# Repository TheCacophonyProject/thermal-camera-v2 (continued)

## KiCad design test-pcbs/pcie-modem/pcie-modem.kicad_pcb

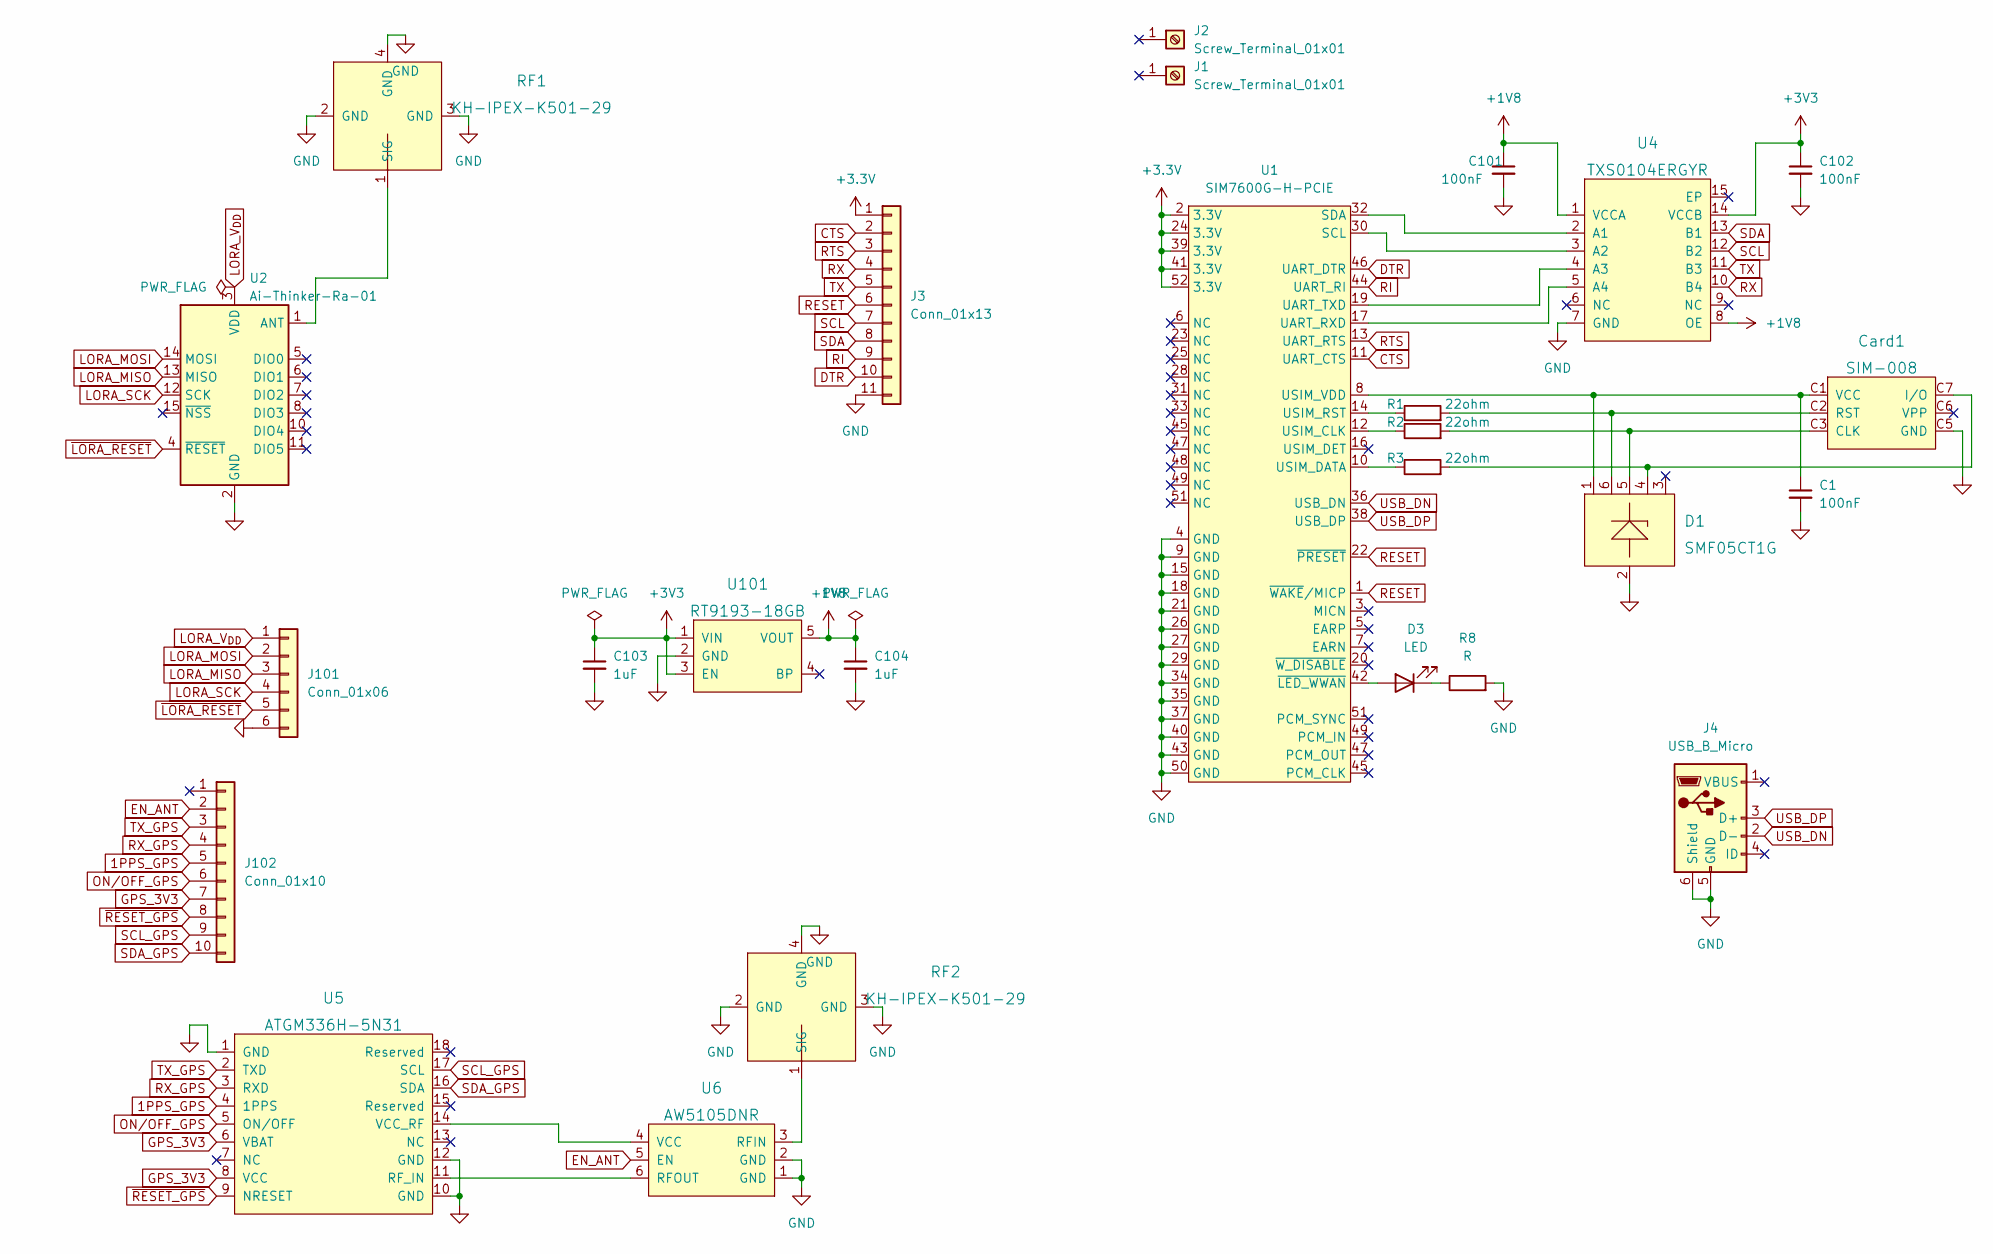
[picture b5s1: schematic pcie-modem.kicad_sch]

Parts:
C1: 100nF; C_0402_1005Metric; LCSC C1525
C101, C102: 100nF; C_0402_1005Metric; LCSC C307331
C103: 1uF; C_0402_1005Metric
C104: 1uF; C_0402_1005Metric; LCSC C52923
Card1: SIM-008; SIM-SMD_SIM-008; LCSC C125618
D1: SMF05CT1G; SOT-363_L2.0-W1.3-P0.65-LS2.1-TL; LCSC C15879
D3: LED; LED_0805_2012Metric; LCSC C84256
J1, J2: Screw_Terminal_01x01; SMD_M2_nut; LCSC C2928176
J3: Conn_01x13; PinHeader_1x11_P2.54mm_Vertical
J4: USB_B_Micro; 920-E52A2021S10100; LCSC C10418
J101: Conn_01x06; PinHeader_1x06_P2.54mm_Vertical
J102: Conn_01x10; PinHeader_1x10_P2.54mm_Vertical
R1, R2, R3: 22ohm; R_0402_1005Metric; LCSC C25092
R8: R; R_0603_1608Metric; LCSC C21190
RF1, RF2: KH-IPEX-K501-29; ANT-SMD_KH-IPEX-K501-29; LCSC C411563
U1: SIM7600G-H-PCIE; BUS_PCI_Express_Mini_Full; LCSC C266898
U2: Ai-Thinker-Ra-01; Ai-Thinker-Ra-01-LoRa; LCSC C90040
U4: TXS0104ERGYR; VQFN-14_L3.5-W3.5-P0.50-BL-EP; JLC Part Extended Part
U5: ATGM336H-5N31; GPSM-SMD_ATGM336H-TR; LCSC C90770
U6: AW5105DNR; DFN-6_L1.5-W1.0-P0.50-BL; LCSC C506193
U101: RT9193-18GB; SOT-23-5; LCSC C27416

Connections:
1PPS_GPS: J102.5, U5.4 (1PPS)
+1V8: C101.1, C104.1, U4.1 (VCCA), U4.8 (OE), U101.5 (VOUT)
CTS: J3.2, U1.11 (UART_CTS)
DTR: J3.10, U1.46 (UART_DTR)
EN_ANT: J102.2, U6.5 (EN)
GND: C1.2, C101.2, C102.2, C103.2, C104.2, Card1.C5 (GND), D1.2, J3.11, J4.5 (GND), J4.6 (Shield), J101.6, R8.2, RF1.2 (GND), RF1.3 (GND), RF1.4 (GND), RF2.2 (GND), RF2.3 (GND), RF2.4 (GND), U1.4 (GND), U1.9 (GND), U1.15 (GND), U1.18 (GND), U1.21 (GND), U1.26 (GND), U1.27 (GND), U1.29 (GND), U1.34 (GND), U1.35 (GND), U1.37 (GND), U1.40 (GND), U1.43 (GND), U1.50 (GND), U2.2 (GND), U2.9 (GND), U2.16 (GND), U4.7 (GND), U5.1 (GND), U5.10 (GND), U5.12 (GND), U6.1 (GND), U6.2 (GND), U101.2 (GND)
GPS_3V3: J102.7, U5.6 (VBAT), U5.8 (VCC)
LORA_MISO: J101.3, U2.13 (MISO)
LORA_MOSI: J101.2, U2.14 (MOSI)
LORA_SCK: J101.4, U2.12 (SCK)
LORA_V_{DD}: J101.1, U2.3 (VDD)
unnamed: C1.1, Card1.C1 (VCC), D1.1, U1.8 (USIM_VDD)
unnamed: Card1.C2 (RST), D1.6, R1.2
unnamed: Card1.C3 (CLK), D1.5, R2.2
unnamed: Card1.C7 (I/O), D1.4, R3.2
unnamed: D3.1 (K), R8.1
unnamed: D3.2 (A), U1.42 (~LED_WWAN)
unnamed: R1.1, U1.14 (USIM_RST)
unnamed: R2.1, U1.12 (USIM_CLK)
unnamed: R3.1, U1.10 (USIM_DATA)
unnamed: RF1.1 (SIG), U2.1 (ANT)
unnamed: RF2.1 (SIG), U6.3 (RFIN)
unnamed: U1.17 (UART_RXD), U4.5 (A4)
unnamed: U1.19 (UART_TXD), U4.4 (A3)
unnamed: U1.30 (SCL), U4.3 (A2)
unnamed: U1.32 (SDA), U4.2 (A1)
unnamed: U5.11 (RF_IN), U6.6 (RFOUT)
unnamed: U5.14 (VCC_RF), U6.4 (VCC)
ON/OFF_GPS: J102.6, U5.5 (ON/OFF)
RESET: J3.6, U1.1 (~WAKE/MICP), U1.22 (~PRESET)
RI: J3.9, U1.44 (UART_RI)
RTS: J3.3, U1.13 (UART_RTS)
RX: J3.4, U4.10 (B4)
RX_GPS: J102.4, U5.3 (RXD)
SCL: J3.7, U4.12 (B2)
SCL_GPS: J102.9, U5.17 (SCL)
SDA: J3.8, U4.13 (B1)
SDA_GPS: J102.10, U5.16 (SDA)
TX: J3.5, U4.11 (B3)
TX_GPS: J102.3, U5.2 (TXD)
USB_DN: J4.2 (D-), U1.36 (USB_DN)
USB_DP: J4.3 (D+), U1.38 (USB_DP)
~LORA_RESET: J101.5, U2.4 (~RESET)
~RESET_GPS: J102.8, U5.9 (NRESET)

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
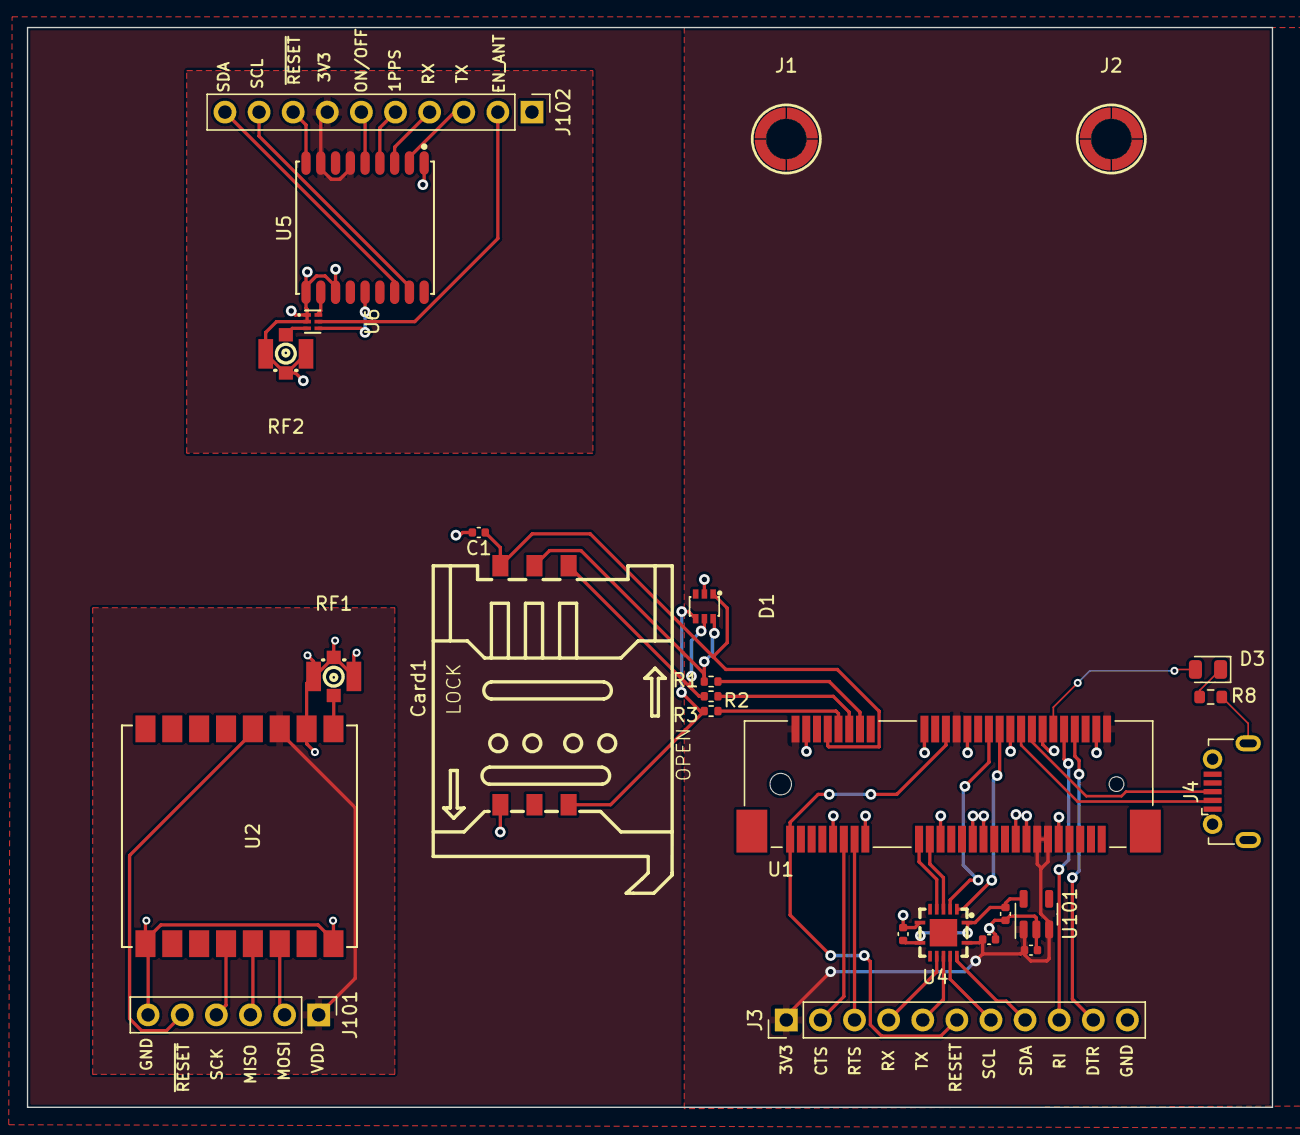
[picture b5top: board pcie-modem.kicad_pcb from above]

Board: 2 copper layers, 92.7 x 80.4 mm, 26 parts (0 on the bottom side), 45 nets.

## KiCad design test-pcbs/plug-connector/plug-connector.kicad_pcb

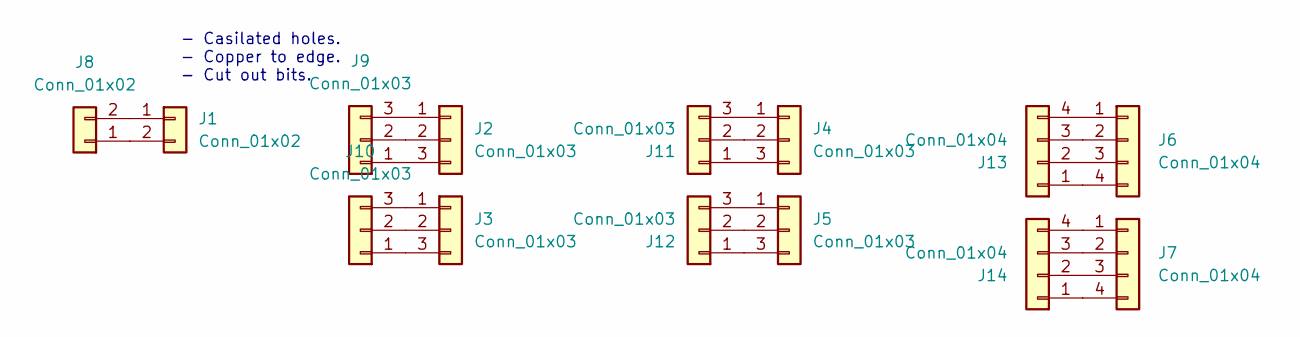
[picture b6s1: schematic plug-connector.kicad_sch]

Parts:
J1: Conn_01x02; m12-2pin
J2: Conn_01x03; m12-3pin
J3: Conn_01x03; m12-3pin-c
J4: Conn_01x03; m16-3pin
J5: Conn_01x03; m16-3pin-c
J6: Conn_01x04; m16-4pin
J7: Conn_01x04; m16-4pin-c
J8: Conn_01x02; PinSocket_1x02_P2.54mm_Vertical
J9, J10, J11, J12: Conn_01x03; PinSocket_1x03_P2.54mm_Vertical
J13, J14: Conn_01x04; PinSocket_1x04_P2.54mm_Vertical

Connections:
unnamed: J1.1, J8.2
unnamed: J1.2, J8.1
unnamed: J2.1, J9.3
unnamed: J2.2, J9.2
unnamed: J2.3, J9.1
unnamed: J3.1, J10.3
unnamed: J3.2, J10.2
unnamed: J3.3, J10.1
unnamed: J4.1, J11.3
unnamed: J4.2, J11.2
unnamed: J4.3, J11.1
unnamed: J5.1, J12.3
unnamed: J5.2, J12.2
unnamed: J5.3, J12.1
unnamed: J6.1, J13.4
unnamed: J6.2, J13.3
unnamed: J6.3, J13.2
unnamed: J6.4, J13.1
unnamed: J7.1, J14.4
unnamed: J7.2, J14.3
unnamed: J7.3, J14.2
unnamed: J7.4, J14.1

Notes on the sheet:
- Casilated holes. - Copper to edge. - Cut out bits.

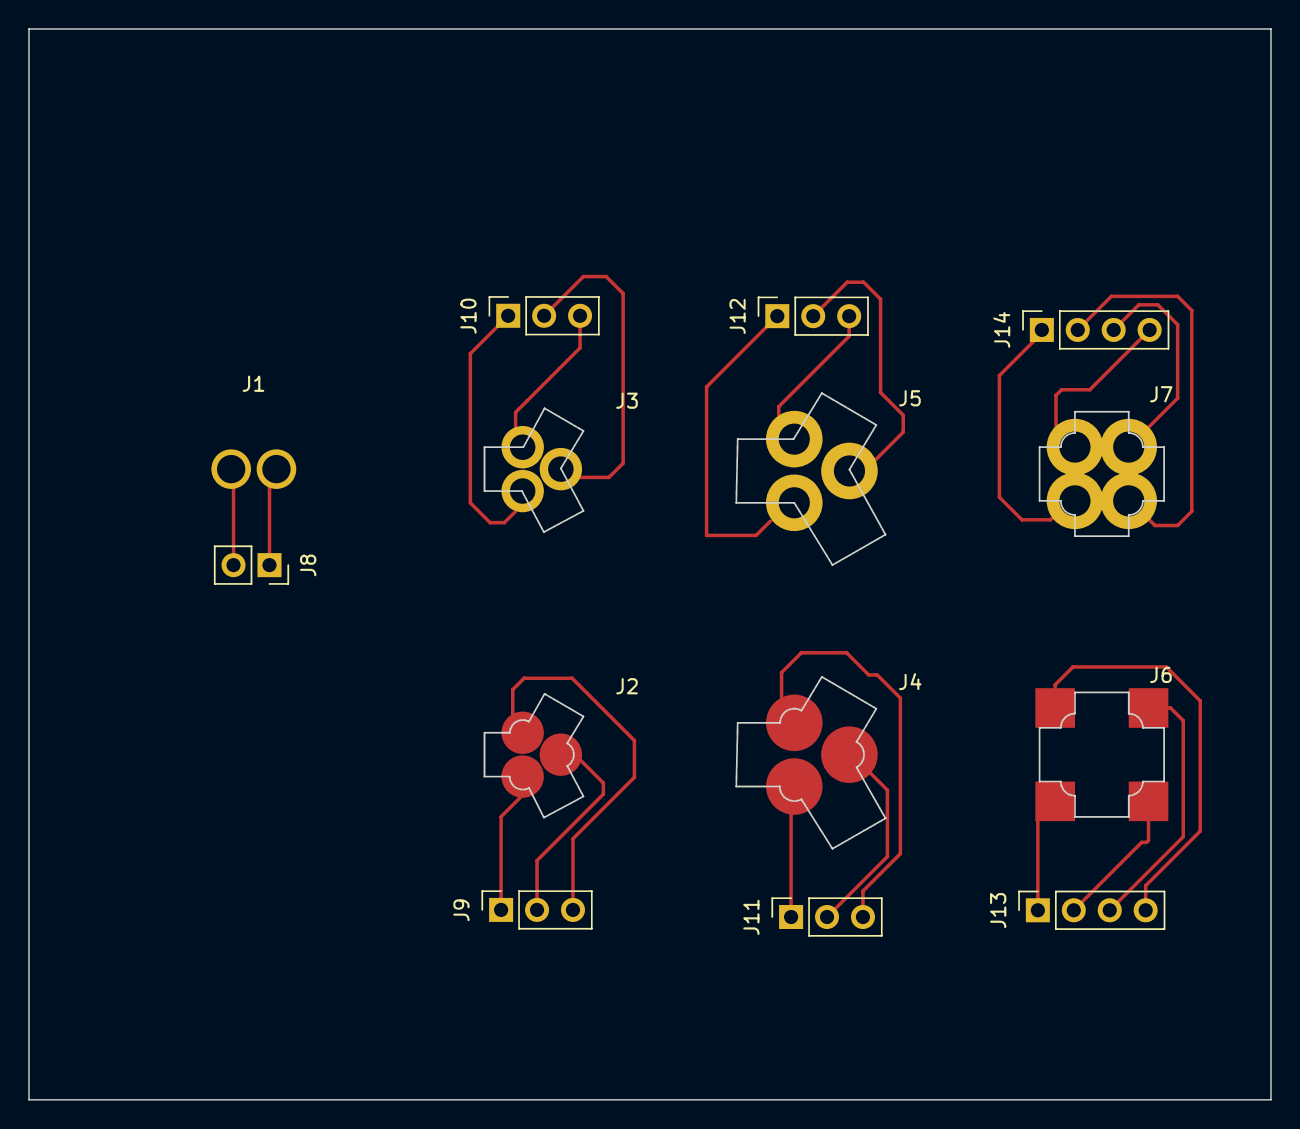
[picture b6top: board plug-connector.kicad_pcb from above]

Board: 2 copper layers, 87.8 x 75.7 mm, 14 parts (0 on the bottom side), 22 nets.

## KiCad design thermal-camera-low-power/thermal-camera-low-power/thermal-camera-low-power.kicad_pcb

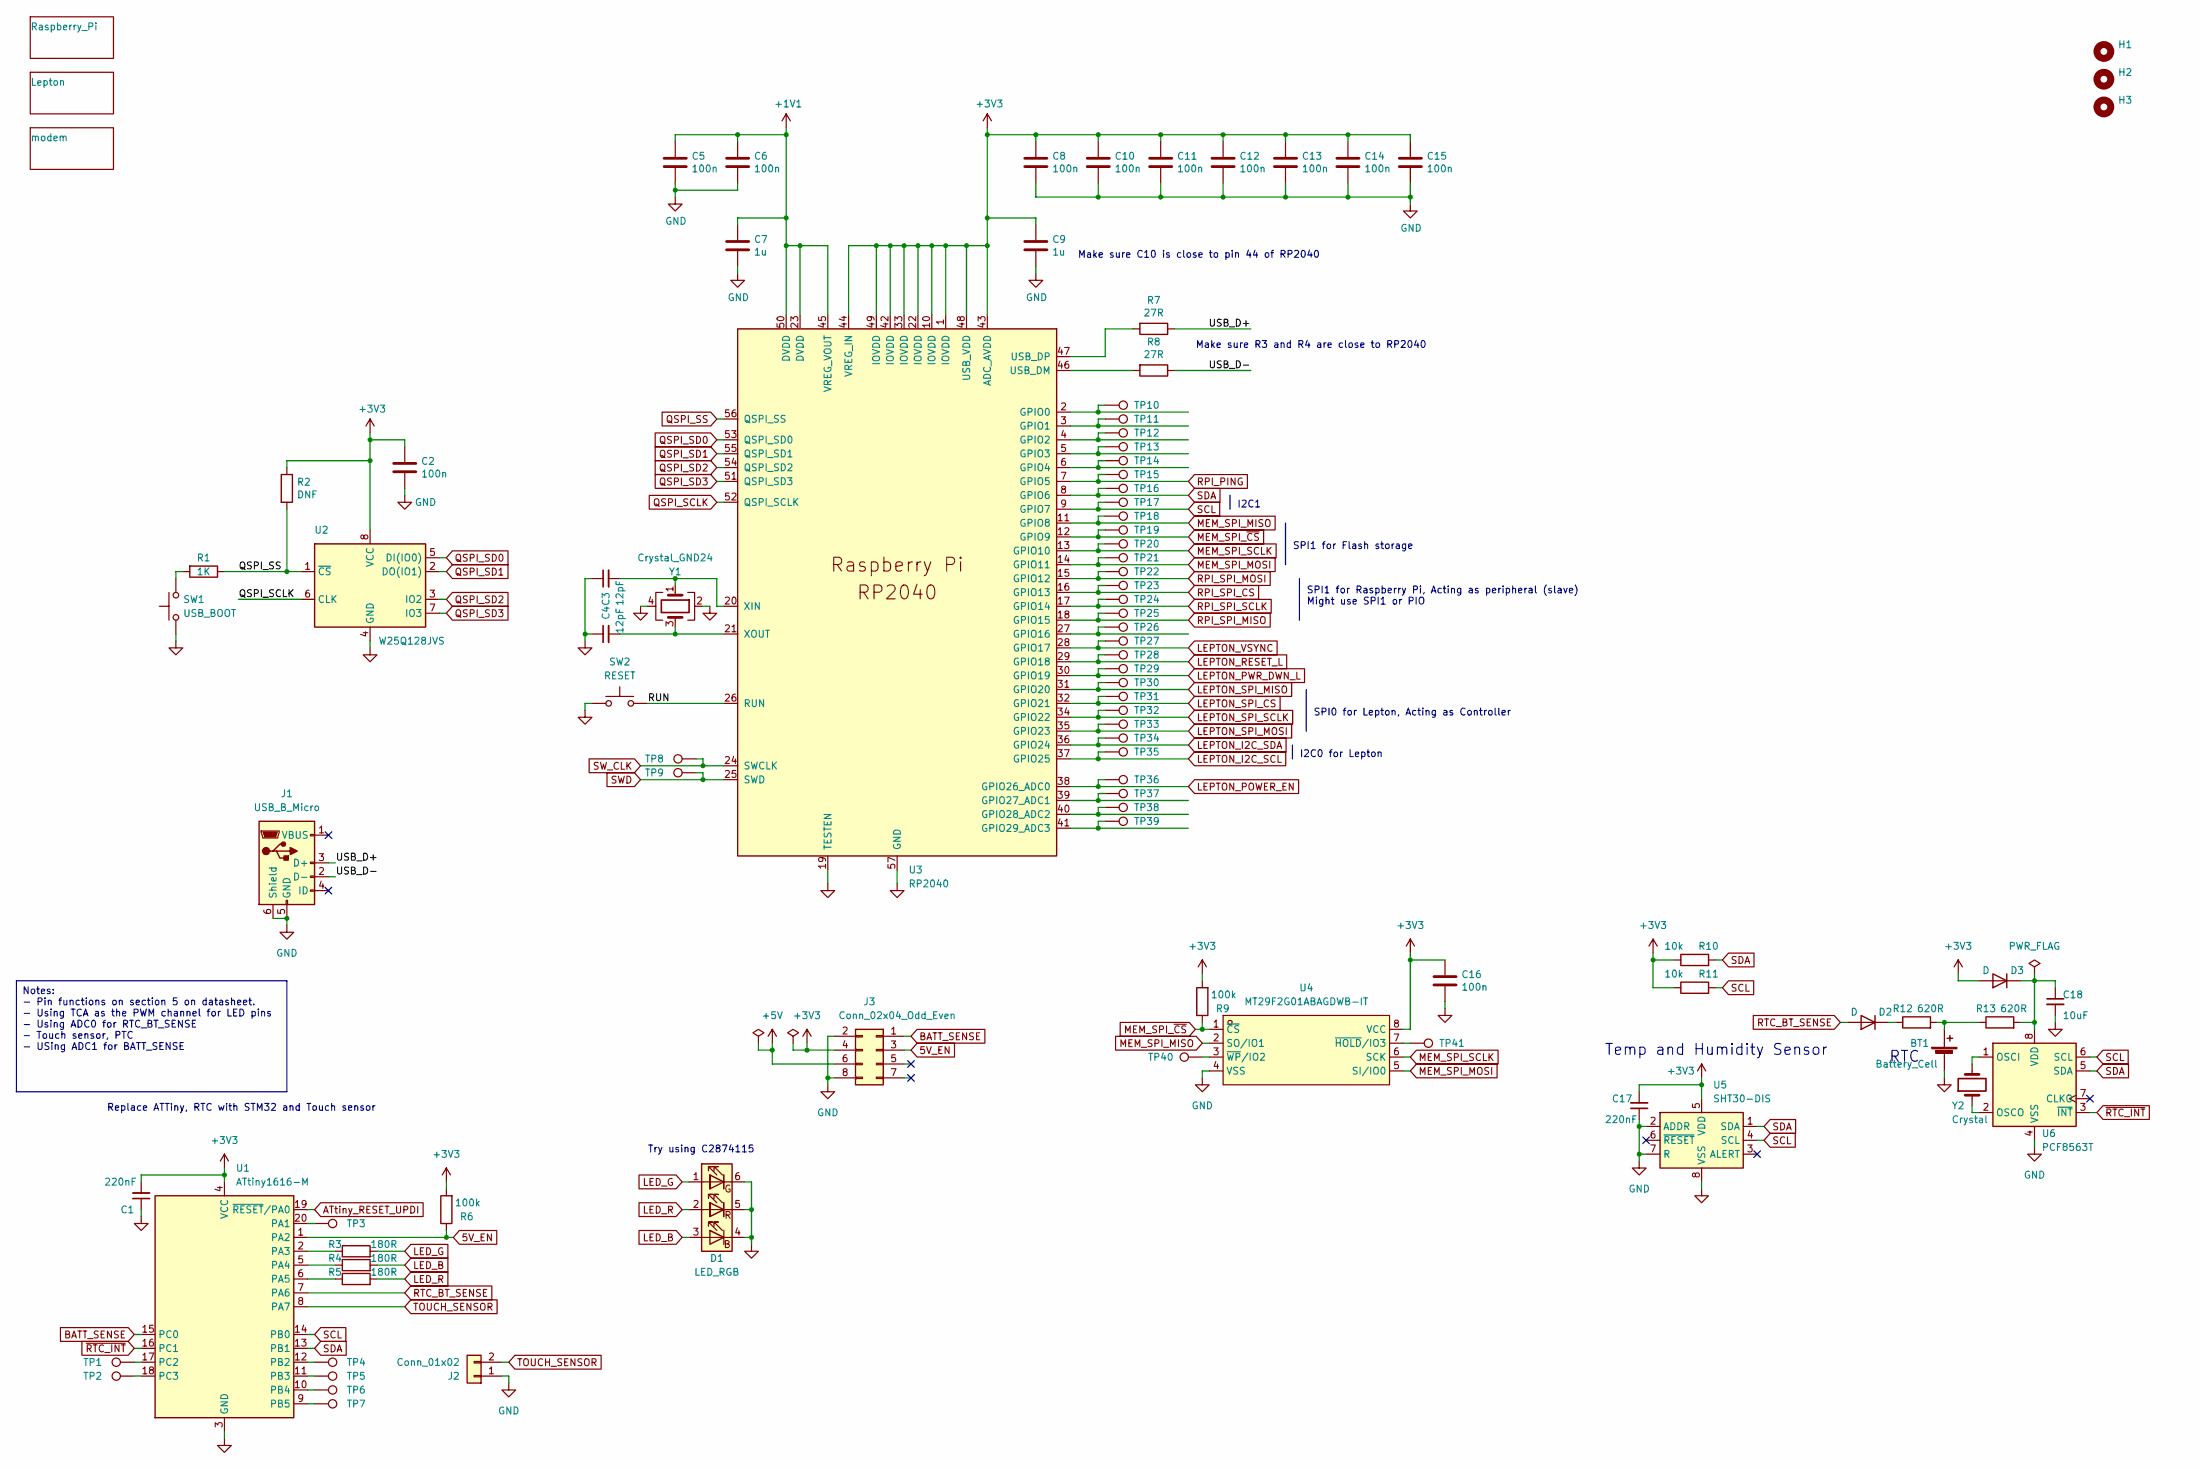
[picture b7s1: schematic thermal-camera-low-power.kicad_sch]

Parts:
BT1: Battery_Cell; CAP-SMD_FL11E
C1, C17: 220nF; C_0402_1005Metric; LCSC C16772
C2, C5, C6, C8, C10, C11, C12, C13, C14, C15, C16: 100n; C_0402_1005Metric; LCSC C307331
C3, C4: 12pF; C_0402_1005Metric; LCSC C1547
C7, C9: 1u; C_0402_1005Metric; LCSC C52923
C18: 10uF; C_0603_1608Metric; LCSC C19702
D1: LED_RGB; LED-SMD_6PIN-L1.60-W1.50-BL-RD; LCSC C375568
D2, D3: D; D_SOD-523; LCSC C668989
H1, H2, H3: MountingHole; Mouning_Hole_M3
J1: USB_B_Micro; MICRO-USB-TH_MICRO-USB-A14; LCSC C145795
J2: Conn_01x02; PinSocket_1x02_P2.54mm_Vertical
J3: Conn_02x04_Odd_Even; power-pcb; LCSC C124386
R1: 1K; R_0402_1005Metric; LCSC C11702
R2: DNF; R_0402_1005Metric
R3, R4, R5: 180R; R_0402_1005Metric; LCSC C38941
R6, R9: 100k; R_0402_1005Metric; LCSC C25741
R7, R8: 27R; R_0603_1608Metric; LCSC C25190
R10, R11: 10k; R_0402_1005Metric; LCSC C25744
R12, R13: 620R; R_0603_1608Metric; LCSC C23220
SW1: USB_BOOT; SW_SPST_SKQG_WithStem; LCSC C318884
SW2: RESET; SW_SPST_SKQG_WithStem; LCSC C318884
TP1, TP2, TP3, TP4, TP5, TP6, TP7, TP8, TP9, TP10, TP11, TP12, TP13, TP14, TP15, TP16, TP17, TP18, TP19, TP20, TP21, TP22, TP23, TP24, TP25, TP26, TP27, TP28, TP29, TP30, TP31, TP32, TP33, TP34, TP35, TP36, TP37, TP38, TP39, TP40, TP41: TestPoint; TP
U1: ATtiny1616-M; VQFN-20-1EP_3x3mm_P0.4mm_EP1.7x1.7mm; LCSC C507118
U2: W25Q128JVS; SOIC-8_5.23x5.23mm_P1.27mm; LCSC C97521
U3: RP2040; RP2040-QFN-56; LCSC C2040
U4: MT29F2G01ABAGDWB-IT; U-PDFN-8_L6.0-W8.0-P1.27-BL; LCSC Part C410863
U5: SHT30-DIS; Sensirion_DFN-8-1EP_2.5x2.5mm_P0.5mm_EP1.1x1.7mm; LCSC C77361
U6: PCF8563T; SOIC-8_3.9x4.9mm_P1.27mm; LCSC C7440
Y1: Crystal_GND24; Crystal_SMD_3225-4Pin_3.2x2.5mm; LCSC C9002
Y2: Crystal; Crystal_SMD_3215-2Pin_3.2x1.5mm; LCSC C32346

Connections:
5V_EN: J3.3, R6.1, U1.1 (PA2)
+1V1: C5.1, C6.1, C7.1, U3.23 (DVDD), U3.45 (VREG_VOUT), U3.50 (DVDD)
+3V3: C1.2, C2.1, C8.1, C9.1, C10.1, C11.1, C12.1, C13.1, C14.1, C15.1, C16.1, C17.2, D3.2 (A), J3.4, R2.1, R6.2, R9.2, R10.1, R11.1, U1.4 (VCC), U2.8 (VCC), U3.1 (IOVDD), U3.10 (IOVDD), U3.22 (IOVDD), U3.33 (IOVDD), U3.42 (IOVDD), U3.43 (ADC_AVDD), U3.44 (VREG_IN), U3.48 (USB_VDD), U3.49 (IOVDD), U4.8 (VCC), U5.5 (VDD); also elsewhere on the board
+5V: J3.6; also elsewhere on the board
/RUN: SW2.2, U3.26 (RUN)
/USB_D+: J1.3 (D+), R7.1
/USB_D-: J1.2 (D-), R8.1
ATtiny_RESET_UPDI: U1.19 (~RESET/PA0); also elsewhere on the board
BATT_SENSE: J3.1, U1.15 (PC0)
GND: BT1.2 (-), C1.1, C2.2, C3.1, C4.1, C5.2, C6.2, C7.2, C8.2, C9.2, C10.2, C11.2, C12.2, C13.2, C14.2, C15.2, C16.2, C17.1, C18.2, D1.4 (BK), D1.5 (GK), D1.6 (RK), J1.5 (GND), J1.6 (Shield), J2.1, J3.2, J3.8, SW1.1, SW2.1, U1.3 (GND), U1.21 (GND), U2.4 (GND), U3.19 (TESTEN), U3.57 (GND), U4.4 (VSS), U5.2 (ADDR), U5.7 (R), U5.8 (VSS), U5.9 (VSS), U6.4 (VSS), Y1.2, Y1.4; also elsewhere on the board
LED_B: D1.3 (BA), R4.2
LED_G: D1.1 (RA), R3.2
LED_R: D1.2 (GA), R5.2
LEPTON_I2C_SCL: TP35.1, U3.37 (GPIO25); also elsewhere on the board
LEPTON_I2C_SDA: TP34.1, U3.36 (GPIO24); also elsewhere on the board
LEPTON_POWER_EN: TP36.1, U3.38 (GPIO26_ADC0); also elsewhere on the board
LEPTON_PWR_DWN_L: TP29.1, U3.30 (GPIO19); also elsewhere on the board
LEPTON_RESET_L: TP28.1, U3.29 (GPIO18); also elsewhere on the board
LEPTON_SPI_CS: TP31.1, U3.32 (GPIO21); also elsewhere on the board
LEPTON_SPI_MISO: TP30.1, U3.31 (GPIO20); also elsewhere on the board
LEPTON_SPI_MOSI: TP33.1, U3.35 (GPIO23); also elsewhere on the board
LEPTON_SPI_SCLK: TP32.1, U3.34 (GPIO22); also elsewhere on the board
LEPTON_VSYNC: TP27.1, U3.28 (GPIO17); also elsewhere on the board
MEM_SPI_MISO: TP18.1, U3.11 (GPIO8), U4.2 (SO/IO1)
MEM_SPI_MOSI: TP21.1, U3.14 (GPIO11), U4.5 (SI/IO0)
MEM_SPI_SCLK: TP20.1, U3.13 (GPIO10), U4.6 (SCK)
MEM_SPI_~CS: R9.1, TP19.1, U3.12 (GPIO9), U4.1 (~CS)
unnamed: BT1.1 (+), R12.2, R13.1
unnamed: C3.2, U3.20 (XIN), Y1.1
unnamed: C4.2, U3.21 (XOUT), Y1.3
unnamed: C18.1, D3.1 (K), R13.2, U6.8 (VDD)
unnamed: D2.1 (K), R12.1
unnamed: R1.2, SW1.2
unnamed: R3.1, U1.2 (PA3)
unnamed: R4.1, U1.5 (PA4)
unnamed: R5.1, U1.6 (PA5)
unnamed: R7.2, U3.47 (USB_DP)
unnamed: R8.2, U3.46 (USB_DM)
unnamed: TP1.1, U1.17 (PC2)
unnamed: TP2.1, U1.18 (PC3)
unnamed: TP3.1, U1.20 (PA1)
unnamed: TP4.1, U1.12 (PB2)
unnamed: TP5.1, U1.11 (PB3)
unnamed: TP6.1, U1.10 (PB4)
unnamed: TP7.1, U1.9 (PB5)
unnamed: TP10.1, U3.2 (GPIO0)
unnamed: TP11.1, U3.3 (GPIO1)
unnamed: TP12.1, U3.4 (GPIO2)
unnamed: TP13.1, U3.5 (GPIO3)
unnamed: TP14.1, U3.6 (GPIO4)
unnamed: TP26.1, U3.27 (GPIO16)
unnamed: TP37.1, U3.39 (GPIO27_ADC1)
unnamed: TP38.1, U3.40 (GPIO28_ADC2)
unnamed: TP39.1, U3.41 (GPIO29_ADC3)
unnamed: TP40.1, U4.3 (~WP/IO2)
unnamed: TP41.1, U4.7 (~HOLD/IO3)
unnamed: U6.1 (OSCI), Y2.2
unnamed: U6.2 (OSCO), Y2.1
QSPI_SCLK: U2.6 (CLK), U3.52 (QSPI_SCLK)
QSPI_SD0: U2.5 (DI(IO0)), U3.53 (QSPI_SD0)
QSPI_SD1: U2.2 (DO(IO1)), U3.55 (QSPI_SD1)
QSPI_SD2: U2.3 (IO2), U3.54 (QSPI_SD2)
QSPI_SD3: U2.7 (IO3), U3.51 (QSPI_SD3)
QSPI_SS: R1.1, R2.2, U2.1 (~CS), U3.56 (QSPI_SS)
RPI_PING: TP15.1, U3.7 (GPIO5); also elsewhere on the board
RPI_SPI_CS: TP23.1, U3.16 (GPIO13); also elsewhere on the board
RPI_SPI_MISO: TP25.1, U3.18 (GPIO15); also elsewhere on the board
RPI_SPI_MOSI: TP22.1, U3.15 (GPIO12); also elsewhere on the board
RPI_SPI_SCLK: TP24.1, U3.17 (GPIO14); also elsewhere on the board
RTC_BT_SENSE: D2.2 (A), U1.7 (PA6)
SCL: R11.2, TP17.1, U1.14 (PB0), U3.9 (GPIO7), U5.4 (SCL), U6.6 (SCL); also elsewhere on the board
SDA: R10.2, TP16.1, U1.13 (PB1), U3.8 (GPIO6), U5.1 (SDA), U6.5 (SDA); also elsewhere on the board
SWD: TP9.1, U3.25 (SWD); also elsewhere on the board
SW_CLK: TP8.1, U3.24 (SWCLK); also elsewhere on the board
TOUCH_SENSOR: J2.2, U1.8 (PA7)
~RTC_INT: U1.16 (PC1), U6.3 (~INT)

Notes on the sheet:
Notes: - Pin functions on section 5 on datasheet. - Using TCA as the PWM channel for LED pins - Using ADC0 for RTC_BT_SENSE - Touch sensor, PTC - USing ADC1 for BATT_SENSE
SPI0 for Lepton, Acting as Controller
Try using C2874115
I2C1
I2C0 for Lepton
Temp and Humidity Sensor
Replace ATTiny, RTC with STM32 and Touch sensor
RTC
Make sure C10 is close to pin 44 of RP2040
SPI1 for Raspberry Pi, Acting as peripheral (slave) Might use SPI1 or PIO
Make sure R3 and R4 are close to RP2040
SPI1 for Flash storage

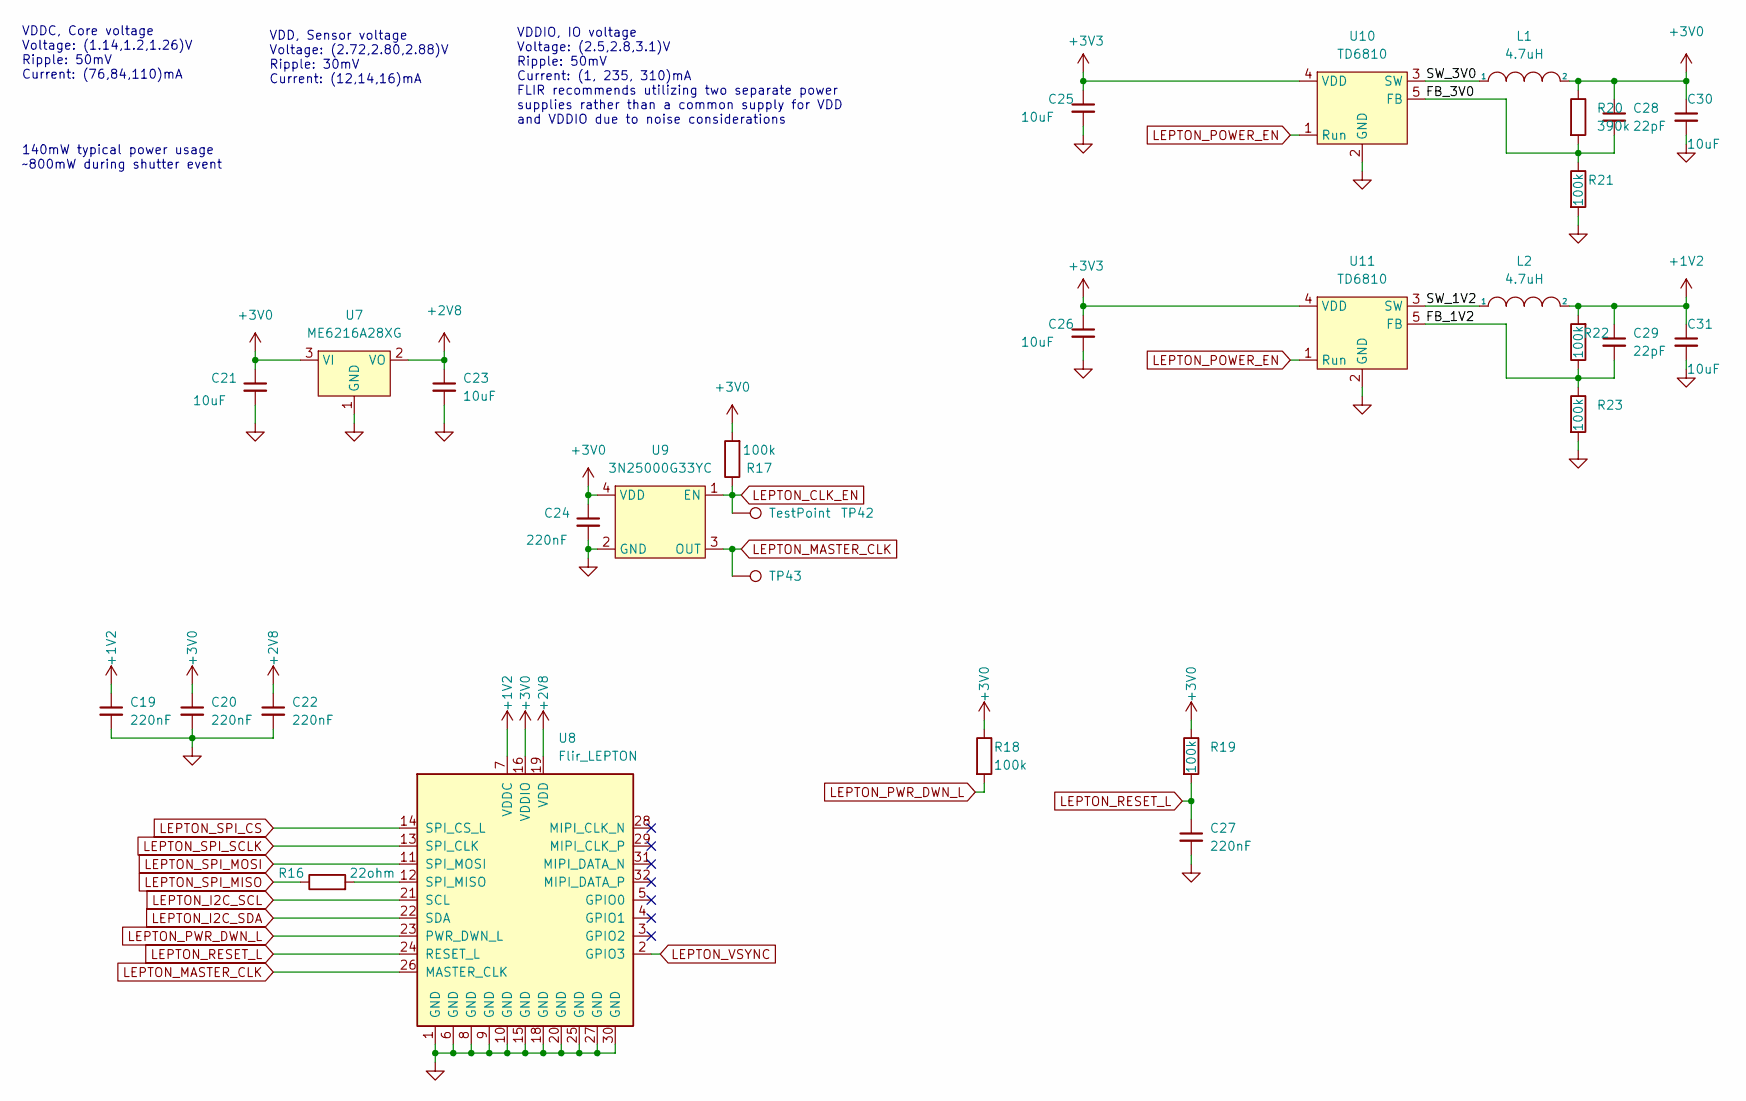
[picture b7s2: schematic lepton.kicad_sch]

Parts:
C19, C20, C22, C24, C27: 220nF; C_0402_1005Metric; LCSC C16772
C21, C23, C25, C26, C30, C31: 10uF; C_0603_1608Metric; LCSC C19702
C28, C29: 22pF; C_0402_1005Metric; LCSC C1555
L1, L2: 4.7uH; IND-SMD_L4.0-W4.0_SWPA4018S; LCSC C354574
R16: 22ohm; R_0402_1005Metric; LCSC C25092
R17: 100k; R_0402_1005Metric; MPN RC1005F103CS; LCSC C25741
R18, R19, R21, R22, R23: 100k; R_0402_1005Metric; LCSC C25741
R20: 390k; R_0402_1005Metric; LCSC C2943536
TP42, TP43: TestPoint; TP
U7: ME6216A28XG; TSOT-23; LCSC C427601
U8: Flir_LEPTON; MOLEX_105028-1001; MPN 1050281001; LCSC C585422
U9: 3N25000G33YC; Oscillator_SMD_Abracon_ASE-4Pin_3.2x2.5mm; LCSC C252341
U10, U11: TD6810; TSOT-23-5; LCSC C16510

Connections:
+1V2: C19.1, C29.1, C31.1, L2.2, R22.2, U8.7 (VDDC)
+2V8: C22.1, C23.1, U7.2 (VO), U8.19 (VDD)
+3V0: C20.1, C21.1, C24.1, C28.1, C30.1, L1.2, R17.2, R18.1, R19.1, R20.1, U7.3 (VI), U8.16 (VDDIO), U9.4 (VDD)
+3V3: C25.1, C26.1, U10.4 (VDD), U11.4 (VDD); also elsewhere on the board
/Lepton/FB_1V2: C29.2, R22.1, R23.1, U11.5 (FB)
/Lepton/FB_3V0: C28.2, R20.2, R21.1, U10.5 (FB)
/Lepton/SW_1V2: L2.1, U11.3 (SW)
/Lepton/SW_3V0: L1.1, U10.3 (SW)
GND: C19.2, C20.2, C21.2, C22.2, C23.2, C24.2, C25.2, C26.2, C27.2, C30.2, C31.2, R21.2, R23.2, U7.1 (GND), U8.1 (GND), U8.6 (GND), U8.8 (GND), U8.9 (GND), U8.10 (GND), U8.15 (GND), U8.18 (GND), U8.20 (GND), U8.25 (GND), U8.27 (GND), U8.30 (GND), U9.2 (GND), U10.2 (GND), U11.2 (GND); also elsewhere on the board
LEPTON_CLK_EN: R17.1, TP42.1, U9.1 (EN)
LEPTON_I2C_SCL: U8.21 (SCL); also elsewhere on the board
LEPTON_I2C_SDA: U8.22 (SDA); also elsewhere on the board
LEPTON_MASTER_CLK: TP43.1, U8.26 (MASTER_CLK), U9.3 (OUT)
LEPTON_POWER_EN: U10.1 (Run), U11.1 (Run); also elsewhere on the board
LEPTON_PWR_DWN_L: R18.2, U8.23 (PWR_DWN_L); also elsewhere on the board
LEPTON_RESET_L: C27.1, R19.2, U8.24 (RESET_L); also elsewhere on the board
LEPTON_SPI_CS: U8.14 (SPI_CS_L); also elsewhere on the board
LEPTON_SPI_MISO: R16.1; also elsewhere on the board
LEPTON_SPI_MOSI: U8.11 (SPI_MOSI); also elsewhere on the board
LEPTON_SPI_SCLK: U8.13 (SPI_CLK); also elsewhere on the board
LEPTON_VSYNC: U8.2 (GPIO3); also elsewhere on the board
unnamed: R16.2, U8.12 (SPI_MISO)

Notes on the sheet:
140mW typical power usage ~800mW during shutter event
VDDC, Core voltage Voltage: (1.14,1.2,1.26)V Ripple: 50mV Current: (76,84,110)mA
VDD, Sensor voltage Voltage: (2.72,2.80,2.88)V Ripple: 30mV Current: (12,14,16)mA
VDDIO, IO voltage Voltage: (2.5,2.8,3.1)V Ripple: 50mV Current: (1, 235, 310)mA FLIR recommends utilizing two separate power supplies rather than a common supply for VDD and VDDIO due to noise considerations

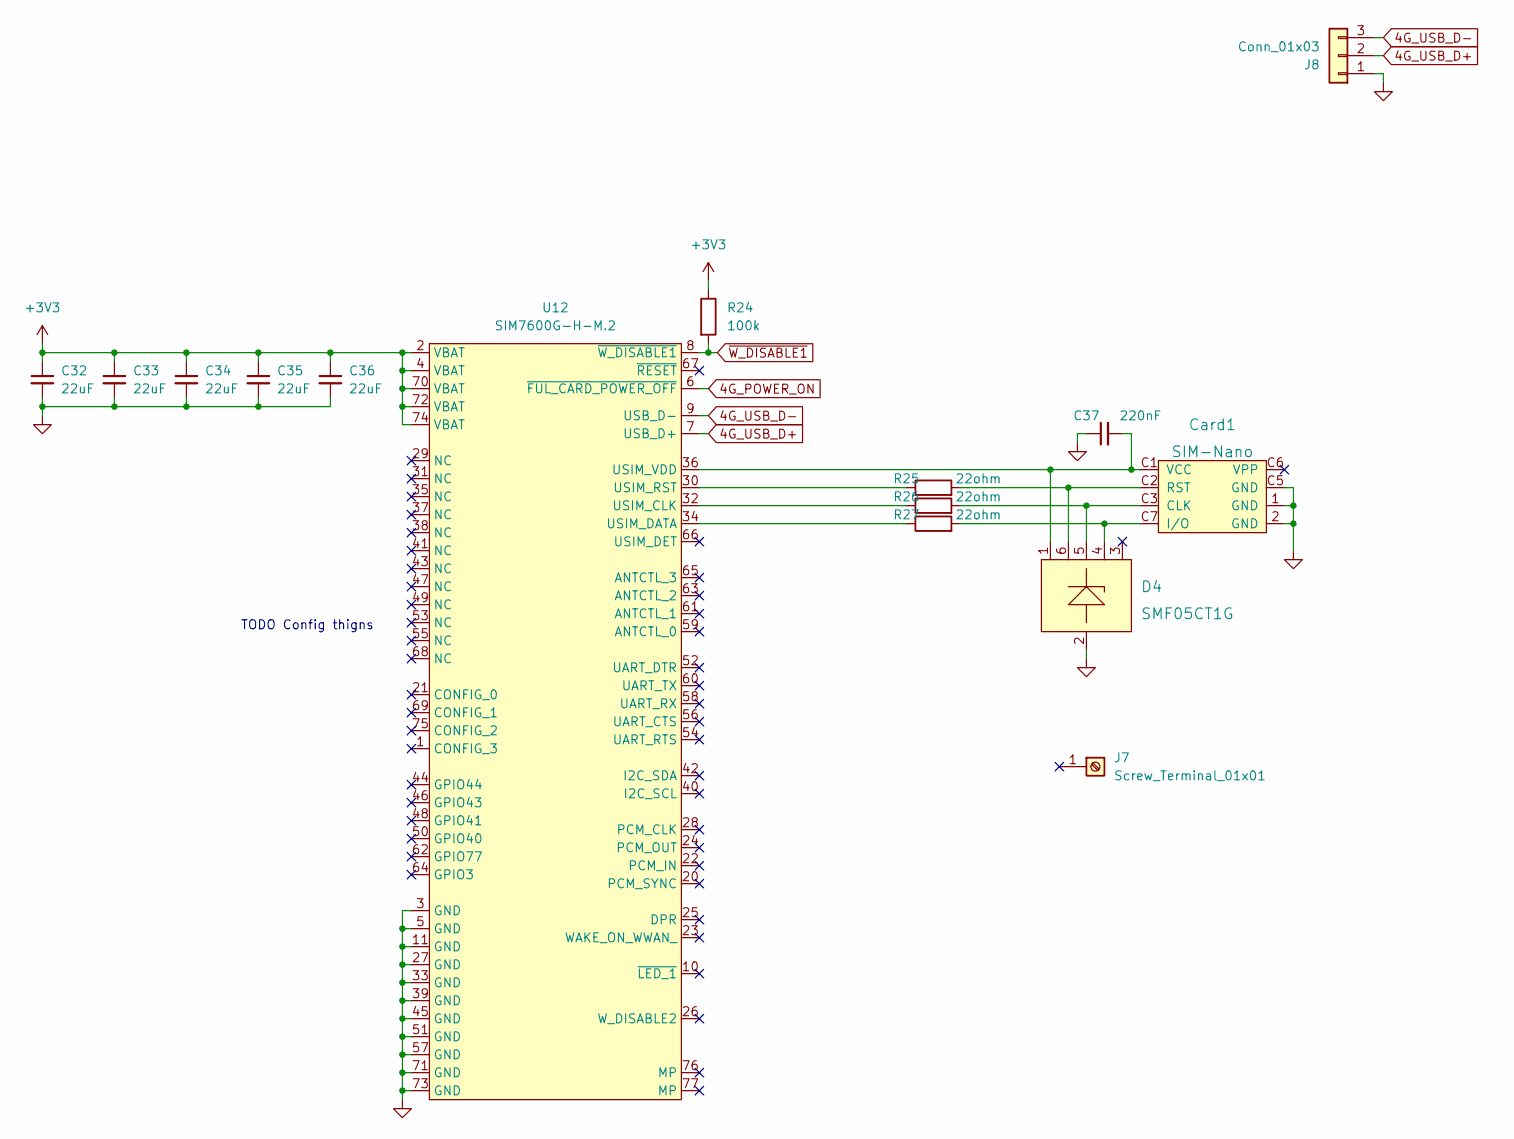
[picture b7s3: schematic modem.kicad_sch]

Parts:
C32, C33, C34, C35, C36: 22uF; C_0603_1608Metric; LCSC C86295
C37: 220nF; C_0402_1005Metric; LCSC C16772
Card1: SIM-Nano; LCSC C266889
D4: SMF05CT1G; SOT-363_L2.0-W1.3-P0.65-LS2.1-TL; LCSC C15879
J7: Screw_Terminal_01x01; SMD_BD4.4-L4.4-D2.8; LCSC C2928178
J8: Conn_01x03; PinHeader_1x03_P2.54mm_Vertical
R24: 100k; R_0402_1005Metric; LCSC C25741
R25, R26, R27: 22ohm; R_0402_1005Metric; LCSC C25092
U12: SIM7600G-H-M.2; M.2; LCSC C2761526

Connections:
4G_POWER_ON: U12.6 (~FUL_CARD_POWER_OFF); also elsewhere on the board
4G_USB_D+: J8.2, U12.7 (USB_D+)
4G_USB_D-: J8.3, U12.9 (USB_D-)
+3V3: C32.1, C33.1, C34.1, C35.1, C36.1, R24.1, U12.2 (VBAT), U12.4 (VBAT), U12.70 (VBAT), U12.72 (VBAT), U12.74 (VBAT); also elsewhere on the board
GND: C32.2, C33.2, C34.2, C35.2, C36.2, C37.1, Card1.1 (GND), Card1.2 (GND), Card1.C5 (GND), D4.2, J8.1, U12.3 (GND), U12.5 (GND), U12.11 (GND), U12.27 (GND), U12.33 (GND), U12.39 (GND), U12.45 (GND), U12.51 (GND), U12.57 (GND), U12.71 (GND), U12.73 (GND); also elsewhere on the board
unnamed: C37.2, Card1.C1 (VCC), D4.1, U12.36 (USIM_VDD)
unnamed: Card1.C2 (RST), D4.6, R25.2
unnamed: Card1.C3 (CLK), D4.5, R26.2
unnamed: Card1.C7 (I/O), D4.4, R27.2
unnamed: R25.1, U12.30 (USIM_RST)
unnamed: R26.1, U12.32 (USIM_CLK)
unnamed: R27.1, U12.34 (USIM_DATA)
~W_DISABLE1: R24.2, U12.8 (~W_DISABLE1); also elsewhere on the board

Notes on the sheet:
TODO Config thigns
